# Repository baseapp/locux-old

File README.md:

locux
=====

Low Cost Open Source Linux SOM, SBC or Core Module in both dip and sodimm packages.

Based on Freescale's IMX233 (ARM926 CPU Running at 454 MHz) , with 32 Kbytes of Integrated Low-Power On-Chip RAM,
64 Kbytes of Integrated Mask-Programmable On-Chip ROM and 512 Mb On-board DDR SDRAM.

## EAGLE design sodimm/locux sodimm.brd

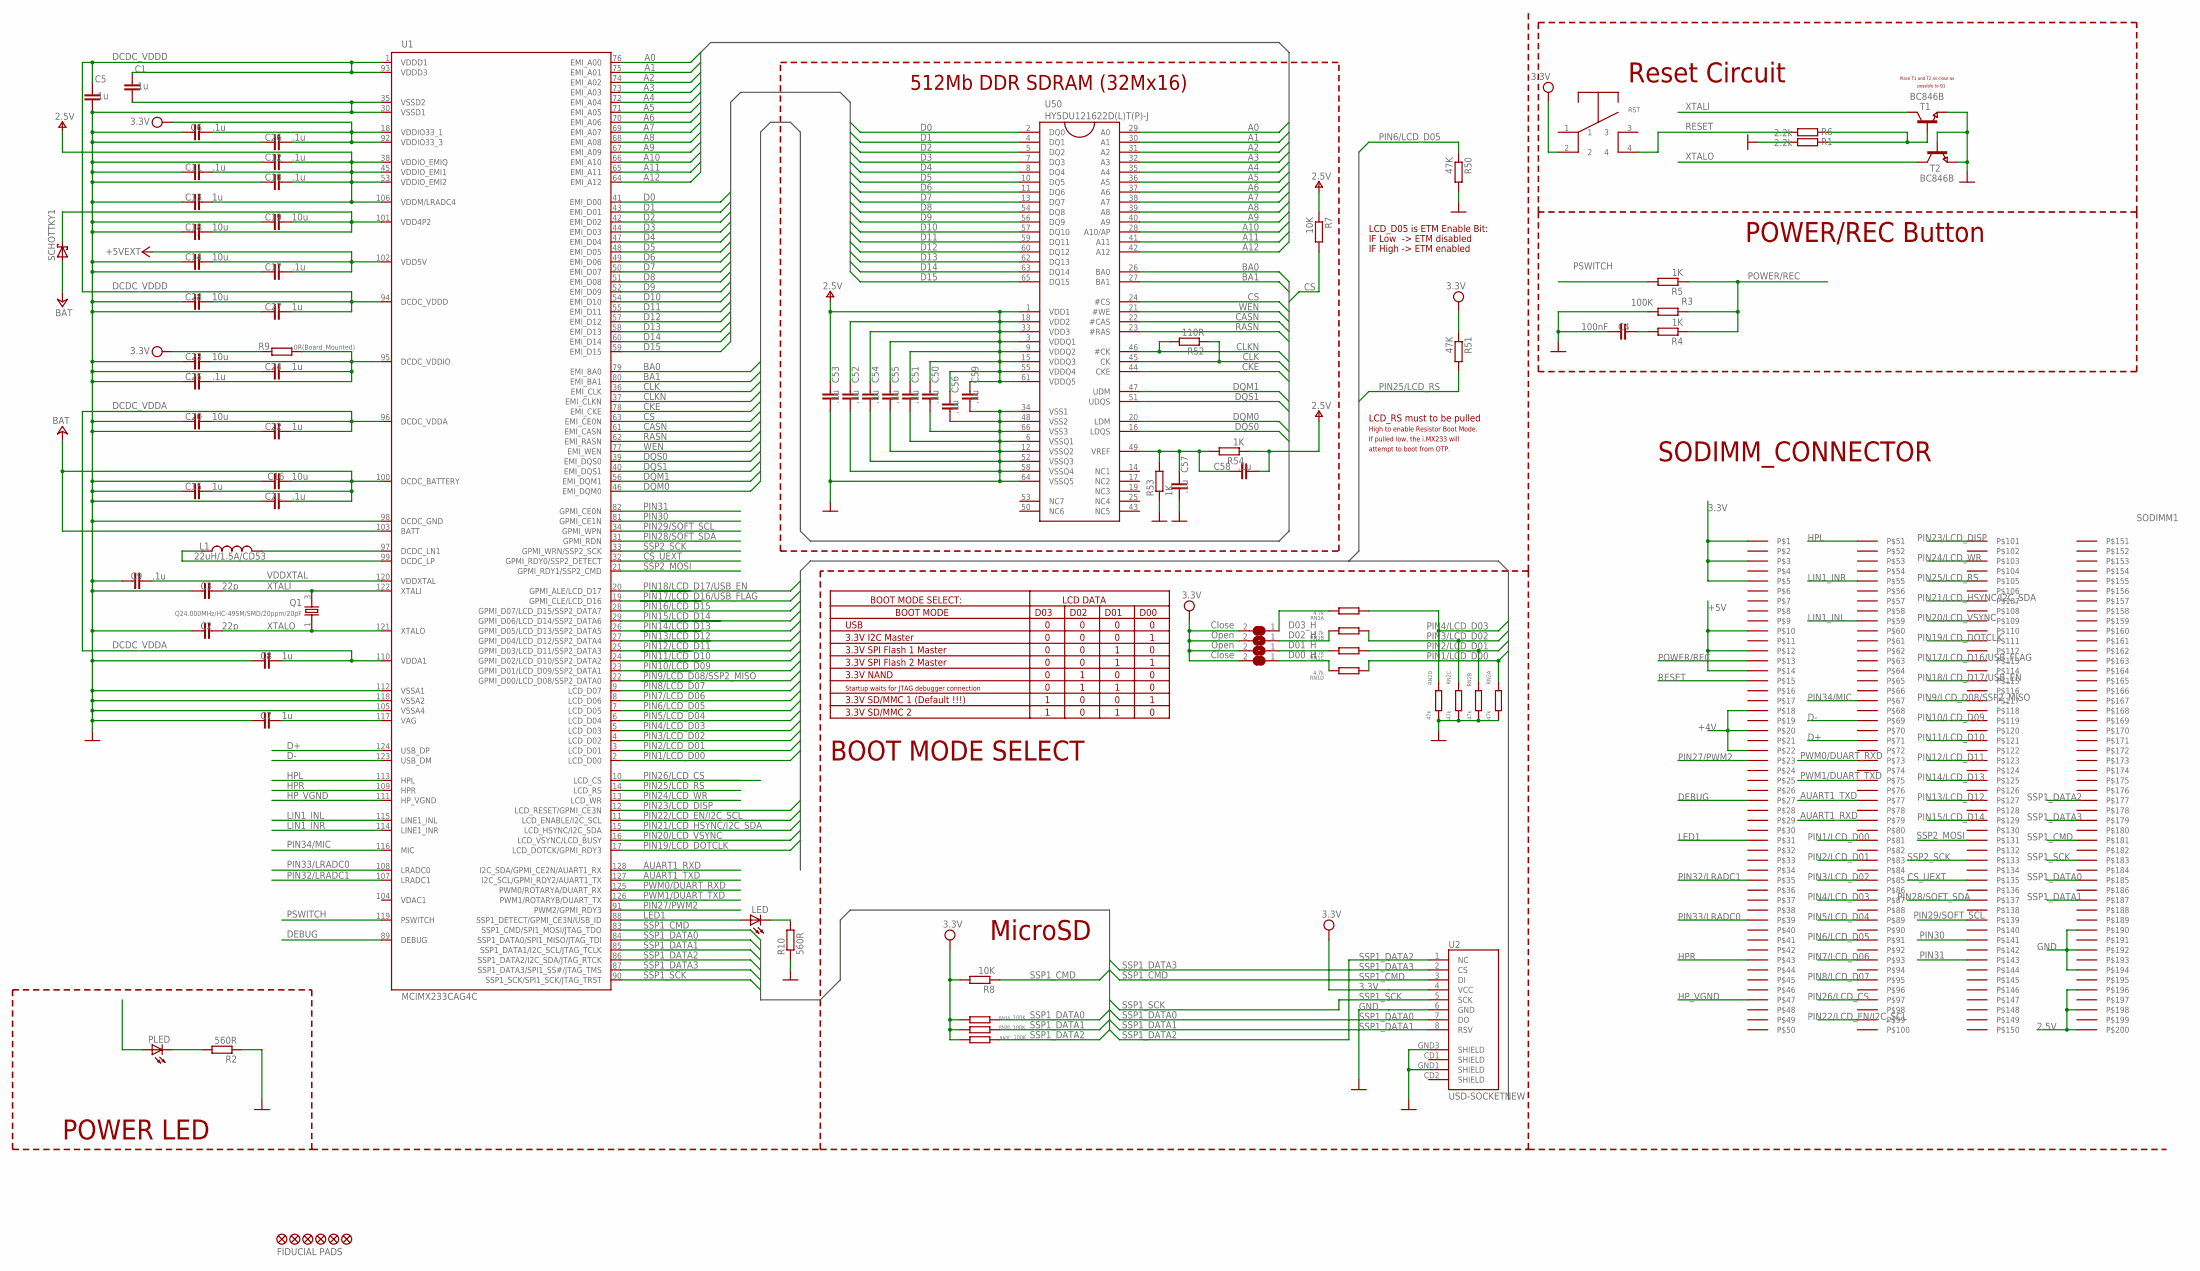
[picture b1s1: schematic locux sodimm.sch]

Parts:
C1, C5, C6, C9, C10, C11, C12, C17, C21, C25, C26, C50, C51, C52, C53, C54, C55, C56, C57, C58, C59: .1u; C0603
C2, C3: 22p; C0603
C4: 100nF; C0603
C7, C8, C13, C15, C22, C24, C27: 1u; C0603
C14, C16, C18, C19, C20, C23, C28: 10u; C0603
D00_H, D03_H: Close; SJ_1_SMALLER
D01_H, D02_H: Open; SJ_1_SMALLER
JP1, JP2, JP3, JP50, JP51, JP52: FIDUCIAL1.5X3; FIDUCIAL-1.5X3
L1: 22uH/1.5A/CD53; NPI75C
LED: LEDCHIP-LED0603; CHIP-LED0603
PLED: LEDCHIP-LED0603; CHIP-LED0603
Q1: Q24.000MHz/HC-49SM/SMD/20ppm/20pF; CRYSTAL-4PIN
R1, R6: 2.2k; R0603
R2, R10: 560R; R0603
R3: 100K; R0603
R4, R5, R53, R54: 1K; R0603
R7, R8: 10K; R0603
R9: 0R(Board_Mounted); R0603
R50, R51: 47K; R0603
R52: 110R; R0603
RN1: 4.7k; 0603-ARC
RN2: 47k; 0603-ARC
RN3: 100K; 0603-ARC
RST: SWITCH_MOMENTARY; SWITCH_SMD
SCHOTTKY1: SCHOTTKY-DIODESMA2; SCHOTTKY_SMA
SODIMM1: SODIMM_BOARDSMALL; SODIMM_BOARD_SMALLER
T1, T2: BC846B; SOT23
U1: MCIMX233CAG4C; TQFP128LD
U2: USD-SOCKETNEW; MICRO-SD-SOCKET-PP
U50: HY5DU121622D(L)T(P)-J; 66TSOP-II

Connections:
2.5V: C10.2, C11.2, C12.2, C13.2, C50.2, C51.2, C52.2, C53.2, C54.2, C55.2, C56.2, C58.1, C59.2, R7.1, R54.1, SODIMM1.196, SODIMM1.198, SODIMM1.200, U1.38 (VDDIO_EMIQ), U1.45 (VDDIO_EMI1), U1.53 (VDDIO_EMI2), U1.106 (VDDM/LRADC4), U50.1 (VDD1), U50.3 (VDDQ1), U50.9 (VDDQ2), U50.15 (VDDQ3), U50.18 (VDD2), U50.33 (VDD3), U50.55 (VDDQ4), U50.61 (VDDQ5)
3.3V: C6.2, C26.2, D00_H.2, D01_H.2, D02_H.2, D03_H.2, PLED.A, R8.2, R9.1, R51.1, RN3.1, RN3.2 (1), RN3.3 (1), RST.2, SODIMM1.1, SODIMM1.3, SODIMM1.5, U1.18 (VDDIO33_1), U1.92 (VDDIO33_3), U2.4 (VCC)
+4V: C15.2, C16.2, C21.2, SCHOTTKY1.A, SODIMM1.18, SODIMM1.20, SODIMM1.22, U1.100 (DCDC_BATTERY), U1.103 (BATT)
+5V: C14.2, C17.2, SODIMM1.10, SODIMM1.12, SODIMM1.14, U1.102 (VDD5V)
A0: U1.76 (EMI_A00), U50.29 (A0)
A1: U1.75 (EMI_A01), U50.30 (A1)
A2: U1.74 (EMI_A02), U50.31 (A2)
A3: U1.73 (EMI_A03), U50.32 (A3)
A4: U1.72 (EMI_A04), U50.35 (A4)
A5: U1.71 (EMI_A05), U50.36 (A5)
A6: U1.70 (EMI_A06), U50.37 (A6)
A7: U1.69 (EMI_A07), U50.38 (A7)
A8: U1.68 (EMI_A08), U50.39 (A8)
A9: U1.67 (EMI_A09), U50.40 (A9)
A10: U1.66 (EMI_A10), U50.28 (A10/AP)
A11: U1.65 (EMI_A11), U50.41 (A11)
A12: U1.64 (EMI_A12), U50.42 (A12)
AUART1_RXD: SODIMM1.79, U1.128 (I2C_SDA/GPMI_CE2N/AUART1_RX)
AUART1_TXD: SODIMM1.77, U1.127 (I2C_SCL/GPMI_RDY2/AUART1_TX)
BA0: U1.79 (EMI_BA0), U50.26 (BA0)
BA1: U1.80 (EMI_BA1), U50.27 (BA1)
CASN: U1.61 (EMI_CASN), U50.22 (#CAS)
CKE: U1.78 (EMI_CKE), U50.44 (CKE)
CLK: R52.1, U1.36 (EMI_CLK), U50.45 (CK)
CLKN: R52.2, U1.37 (EMI_CLKN), U50.46 (#CK)
CS: R7.2, U1.63 (EMI_CE0N), U50.24 (#CS)
CS_UEXT: SODIMM1.135, U1.32 (GPMI_RDY0/SSP2_DETECT)
D0: U1.41 (EMI_D00), U50.2 (DQ0)
D1: U1.43 (EMI_D01), U50.4 (DQ1)
D2: U1.42 (EMI_D02), U50.5 (DQ2)
D3: U1.44 (EMI_D03), U50.7 (DQ3)
D4: U1.47 (EMI_D04), U50.8 (DQ4)
D5: U1.48 (EMI_D05), U50.10 (DQ5)
D6: U1.49 (EMI_D06), U50.11 (DQ6)
D7: U1.50 (EMI_D07), U50.13 (DQ7)
D8: U1.51 (EMI_D08), U50.54 (DQ8)
D9: U1.52 (EMI_D09), U50.56 (DQ9)
D10: U1.54 (EMI_D10), U50.57 (DQ10)
D11: U1.55 (EMI_D11), U50.59 (DQ11)
D12: U1.57 (EMI_D12), U50.60 (DQ12)
D13: U1.58 (EMI_D13), U50.62 (DQ13)
D14: U1.60 (EMI_D14), U50.63 (DQ14)
D15: U1.59 (EMI_D15), U50.65 (DQ15)
D+: SODIMM1.71, U1.124 (USB_DP)
D-: SODIMM1.69, U1.123 (USB_DM)
DCDC_VDDA: C8.2, C20.2, C22.2, U1.96 (DCDC_VDDA), U1.110 (VDDA1)
DCDC_VDDD: C1.2, C5.2, C27.2, C28.2, U1.1 (VDDD1), U1.93 (VDDD3), U1.94 (DCDC_VDDD)
DCDC_VDDIO: C23.2, C24.2, C25.2, R9.2, U1.95 (DCDC_VDDIO)
DEBUG: SODIMM1.27, U1.89 (DEBUG)
DQM0: U1.46 (EMI_DQM0), U50.20 (LDM)
DQM1: U1.56 (EMI_DQM1), U50.47 (UDM)
DQS0: U1.39 (EMI_DQS0), U50.16 (LDQS)
DQS1: U1.40 (EMI_DQS1), U50.51 (UDQS)
GND: C1.1, C2.1, C3.1, C4.2, C5.1, C6.1, C7.1, C8.1, C9.1, C10.1, C11.1, C12.1, C13.1, C14.1, C15.1, C16.1, C17.1, C18.1, C19.1, C20.1, C21.1, C22.1, C23.1, C24.1, C25.1, C26.1, C27.1, C28.1, C50.1, C51.1, C52.1, C53.1, C54.1, C55.1, C56.1, C57.1, C59.1, R1.2, R2.1, R3.2, R10.1, R50.2, R53.1, RN2.5 (2), RN2.6 (2), RN2.7 (2), RN2.8 (2), SODIMM1.190, SODIMM1.192, SODIMM1.194, T1.2 (E), T2.1 (B), T2.2 (E), U1.30 (VSSD1), U1.35 (VSSD2), U1.98 (DCDC_GND), U1.105 (VSSA4), U1.112 (VSSA1), U1.118 (VSSA2), U2.6 (GND), U2.GND1 (SHIELD), U2.GND3 (SHIELD), U50.6 (VSSQ1), U50.12 (VSSQ2), U50.34 (VSS1), U50.48 (VSS2), U50.52 (VSSQ3), U50.58 (VSSQ4), U50.64 (VSSQ5), U50.66 (VSS3)
HPL: SODIMM1.51, U1.113 (HPL)
HPR: SODIMM1.43, U1.109 (HPR)
HP_VGND: SODIMM1.47, U1.111 (HP_VGND)
LED1: LED.A, SODIMM1.31, U1.88 (SSP1_DETECT/GPMI_CE3N/USB_ID)
LIN1_INL: SODIMM1.59, U1.115 (LINE1_INL)
LIN1_INR: SODIMM1.55, U1.114 (LINE1_INR)
unnamed: D03_H.1, RN1.8 (2)
unnamed: LED.C, R10.2
unnamed: PLED.C, R2.2
unnamed: C57.2, C58.2, R53.2, R54.2, U50.49 (VREF)
unnamed: L1.2, U1.97 (DCDC_LN1)
unnamed: L1.1, U1.99 (DCDC_LP)
unnamed: C7.2, U1.117 (VAG)
unnamed: C4.1, R4.2
unnamed: R1.1, R6.1, T1.1 (B)
unnamed: D02_H.1, RN1.7 (2)
unnamed: D01_H.1, RN1.6 (2)
unnamed: D00_H.1, RN1.5 (2)
PIN1/LCD_D00: RN1.4 (1), RN2.1, SODIMM1.81, U1.2 (LCD_D00)
PIN2/LCD_D01: RN1.3 (1), RN2.2 (1), SODIMM1.83, U1.3 (LCD_D01)
PIN3/LCD_D02: RN1.2 (1), RN2.3 (1), SODIMM1.85, U1.4 (LCD_D02)
PIN4/LCD_D03: RN1.1, RN2.4 (1), SODIMM1.87, U1.5 (LCD_D03)
PIN5/LCD_D04: SODIMM1.89, U1.6 (LCD_D04)
PIN6/LCD_D05: R50.1, SODIMM1.91, U1.7 (LCD_D05)
PIN7/LCD_D06: SODIMM1.93, U1.8 (LCD_D06)
PIN8/LCD_D07: SODIMM1.95, U1.9 (LCD_D07)
PIN9/LCD_D08/SSP2_MISO: SODIMM1.117, U1.22 (GPMI_D00/LCD_D08/SSP2_DATA0)
PIN10/LCD_D09: SODIMM1.119, U1.23 (GPMI_D01/LCD_D09/SSP2_DATA1)
PIN11/LCD_D10: SODIMM1.121, U1.24 (GPMI_D02/LCD_D10/SSP2_DATA2)
PIN12/LCD_D11: SODIMM1.123, U1.25 (GPMI_D03/LCD_D11/SSP2_DATA3)
PIN13/LCD_D12: SODIMM1.127, U1.27 (GPMI_D04/LCD_D12/SSP2_DATA4)
PIN14/LCD_D13: SODIMM1.125, U1.26 (GPMI_D05/LCD_D13/SSP2_DATA5)
PIN15/LCD_D14: SODIMM1.129, U1.29 (GPMI_D06/LCD_D14/SSP2_DATA6)
PIN16/LCD_D15: U1.28 (GPMI_D07/LCD_D15/SSP2_DATA7)
PIN17/LCD_D16/USB_FLAG: SODIMM1.113, U1.19 (GPMI_CLE/LCD_D16)
PIN18/LCD_D17/USB_EN: SODIMM1.115, U1.20 (GPMI_ALE/LCD_D17)
PIN19/LCD_DOTCLK: SODIMM1.111, U1.17 (LCD_DOTCK/GPMI_RDY3)
PIN20/LCD_VSYNC: SODIMM1.109, U1.16 (LCD_VSYNC/LCD_BUSY)
PIN21/LCD_HSYNC/I2C_SDA: SODIMM1.107, U1.15 (LCD_HSYNC/I2C_SDA)
PIN22/LCD_EN/I2C_SCL: SODIMM1.99, U1.11 (LCD_ENABLE/I2C_SCL)
PIN23/LCD_DISP: SODIMM1.101, U1.12 (LCD_RESET/GPMI_CE3N)
PIN24/LCD_WR: SODIMM1.103, U1.13 (LCD_WR)
PIN25/LCD_RS: R51.2, SODIMM1.105, U1.14 (LCD_RS)
PIN26/LCD_CS: SODIMM1.97, U1.10 (LCD_CS)
PIN27/PWM2: SODIMM1.23, U1.91 (PWM2/GPMI_RDY3)
PIN28/SOFT_SDA: SODIMM1.133, U1.31 (GPMI_RDN)
PIN29/SOFT_SCL: SODIMM1.139, U1.34 (GPMI_WPN)
PIN30: SODIMM1.141, U1.81 (GPMI_CE1N)
PIN31: SODIMM1.143, U1.82 (GPMI_CE0N)
PIN32/LRADC1: SODIMM1.35, U1.107 (LRADC1)
PIN33/LRADC0: SODIMM1.39, U1.108 (LRADC0)
PIN34/MIC: SODIMM1.67, U1.116 (MIC)
POWER/REC: R3.1, R4.1, R5.1, SODIMM1.13
PSWITCH: R5.2, U1.119 (PSWITCH)
PWM0/DUART_RXD: SODIMM1.73, U1.125 (PWM0/ROTARYA/DUART_RX)
PWM1/DUART_TXD: SODIMM1.75, U1.126 (PWM1/ROTARYB/DUART_TX)
RASN: U1.62 (EMI_RASN), U50.23 (#RAS)
RESET: R6.2, RST.4, SODIMM1.15
SSP1_CMD: R8.1, SODIMM1.181, U1.83 (SSP1_CMD/SPI1_MOSI/JTAG_TDO), U2.3 (DI)
SSP1_DATA0: RN3.8 (2), SODIMM1.185, U1.84 (SSP1_DATA0/SPI1_MISO/JTAG_TDI), U2.7 (DO)
SSP1_DATA1: RN3.7 (2), SODIMM1.187, U1.85 (SSP1_DATA1/I2C_SCL/JTAG_TCLK), U2.8 (RSV)
SSP1_DATA2: RN3.6 (2), SODIMM1.177, U1.86 (SSP1_DATA2/I2C_SDA/JTAG_RTCK), U2.1 (NC)
SSP1_DATA3: SODIMM1.179, U1.87 (SSP1_DATA3/SPI1_SS#/JTAG_TMS), U2.2 (CS)
SSP1_SCK: SODIMM1.183, U1.90 (SSP1_SCK/SPI1_SCK/JTAG_TRST), U2.5 (SCK)
SSP2_MOSI: SODIMM1.131, U1.21 (GPMI_RDY1/SSP2_CMD)
SSP2_SCK: SODIMM1.137, U1.33 (GPMI_WRN/SSP2_SCK)
VDD4P2: C18.2, C19.2, SCHOTTKY1.C, U1.101 (VDD4P2)
VDDXTAL: C9.2, U1.120 (VDDXTAL)
WEN: U1.77 (EMI_WEN), U50.21 (#WE)
XTALI: C3.2, Q1.3 (2), T1.3 (C), U1.122 (XTALI)
XTALO: C2.2, Q1.1, T2.3 (C), U1.121 (XTALO)

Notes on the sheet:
512Mb DDR SDRAM (32Mx16)
MicroSD
POWER/REC Button
BOOT MODE SELECT
BOOT MODE SELECT:
LCD DATA
BOOT MODE
D03
D02
D01
D00
USB
3.3V I2C Master
3.3V SPI Flash 1 Master
3.3V SPI Flash 2 Master
3.3V NAND
Startup waits for JTAG debugger connection
3.3V SD/MMC 1 (Default !!!)
3.3V SD/MMC 2
LCD_RS must to be pulled
High to enable Resistor Boot Mode.
If pulled low, the i.MX233 will
attempt to boot from OTP.
LCD_D05 is ETM Enable Bit:
IF Low -> ETM disabled
IF High -> ETM enabled
Place T1 and T2 as close as
possible to Q1
Reset Circuit
SODIMM_CONNECTOR
FIDUCIAL PADS
POWER LED

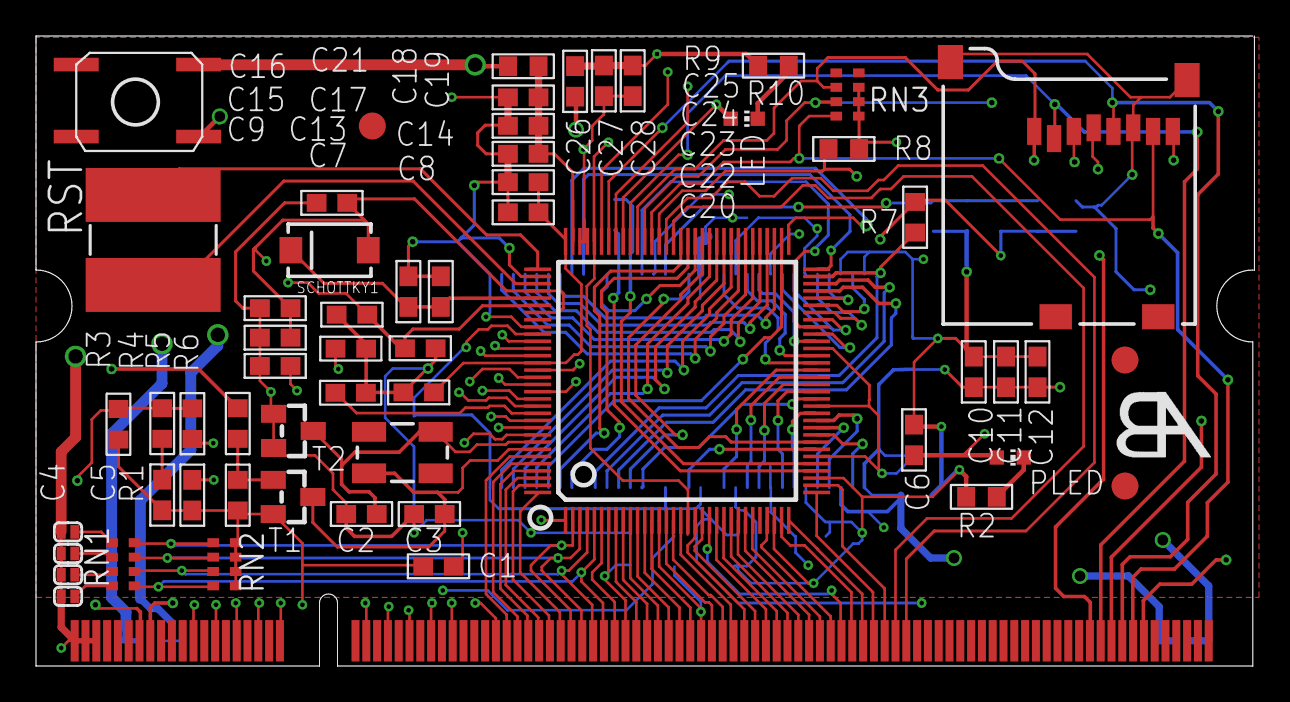
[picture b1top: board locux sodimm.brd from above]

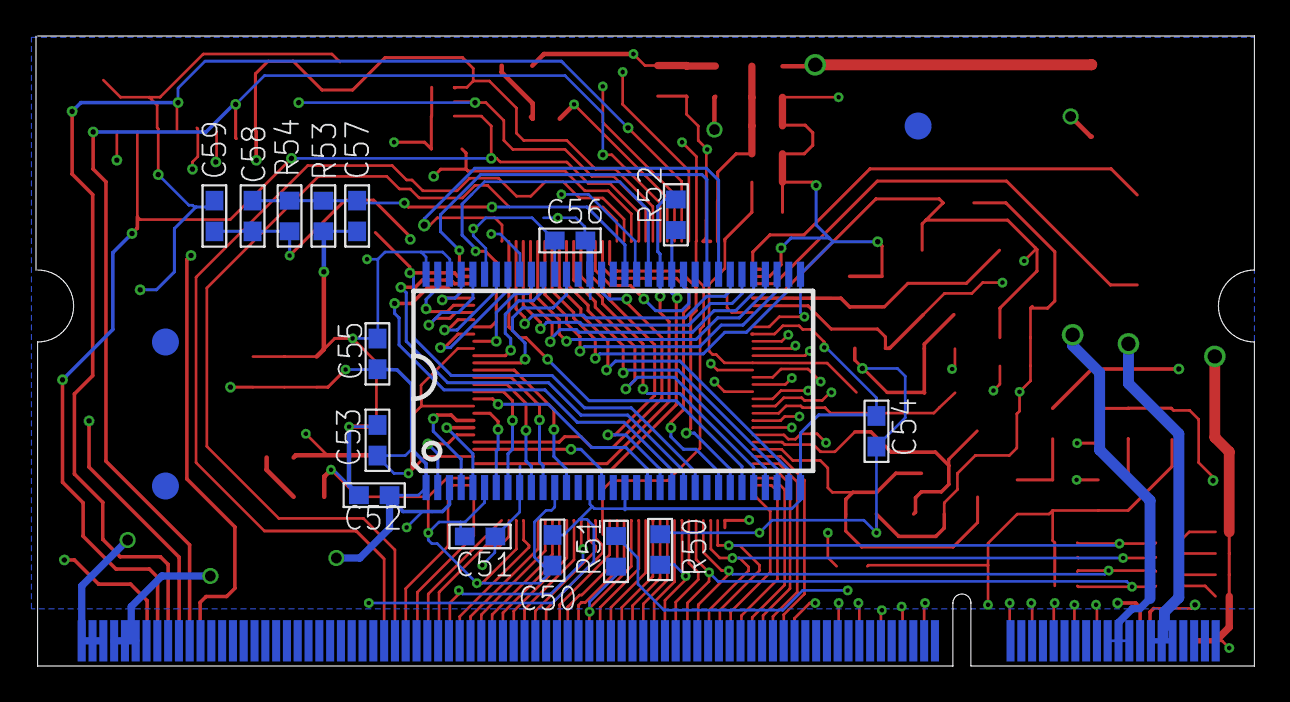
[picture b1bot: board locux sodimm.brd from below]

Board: 4 copper layers, 67.7 x 35.0 mm, 78 parts (19 on the bottom side), 124 nets.

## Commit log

2012-05-21 Gerbers and Schematics
2013-01-07 Sodimm.
2013-01-07 Sodimm form factor - eagle schematics and gerber

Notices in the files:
parts and their libraries:
SparkFun: Licensing: CC v3.0 Share-Alike You are welcome to use this library for commercial purposes.
